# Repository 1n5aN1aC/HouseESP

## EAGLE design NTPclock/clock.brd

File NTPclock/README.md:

TODO:

4 control buttons.
  hour offset
  minute offset
  brightness control
2 segment seperator LEDs
bar graph seconds display.
1 randimizer LED.
12/24h switch

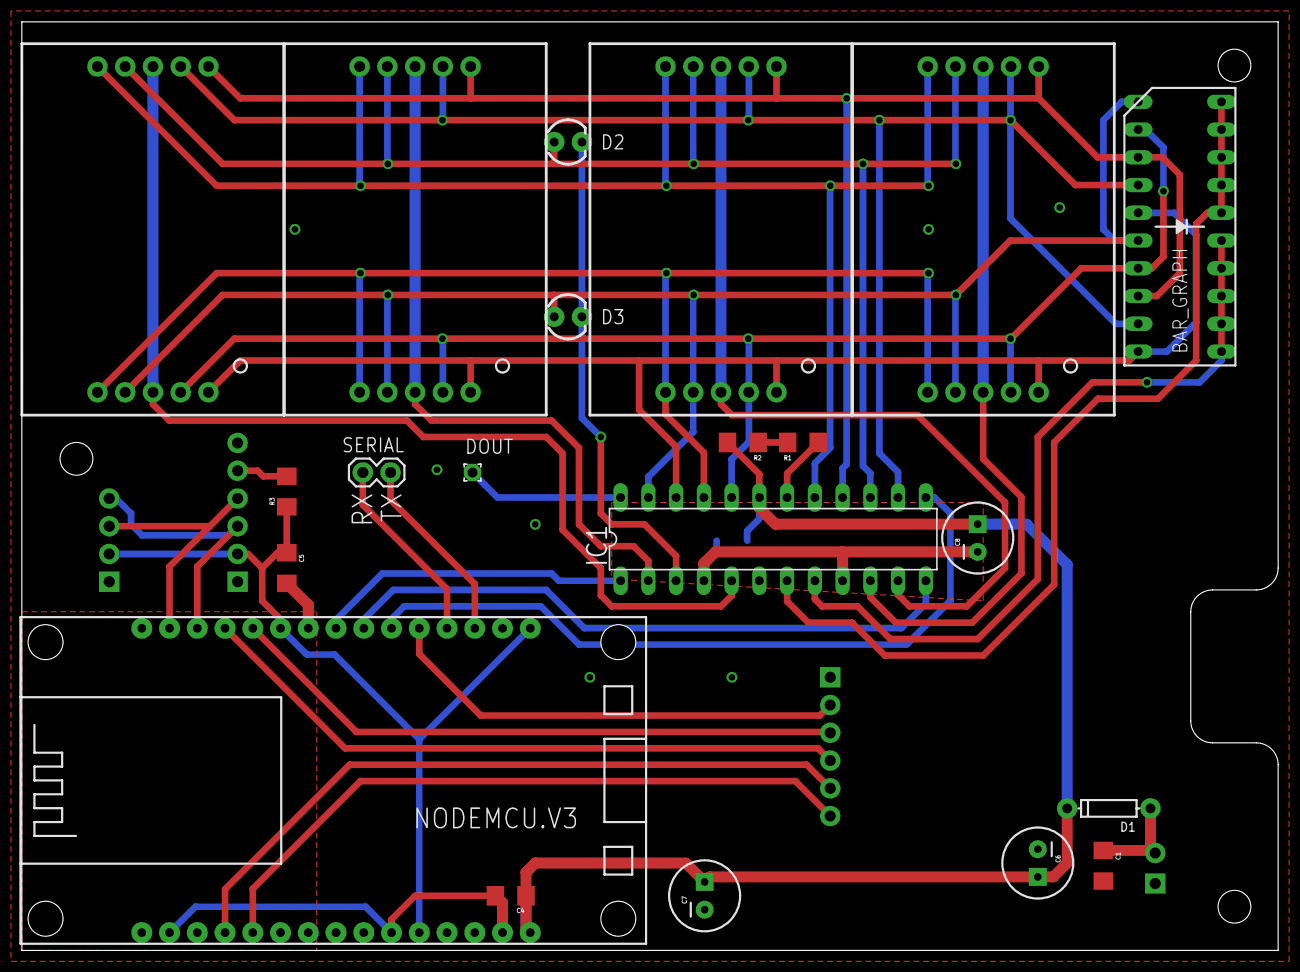
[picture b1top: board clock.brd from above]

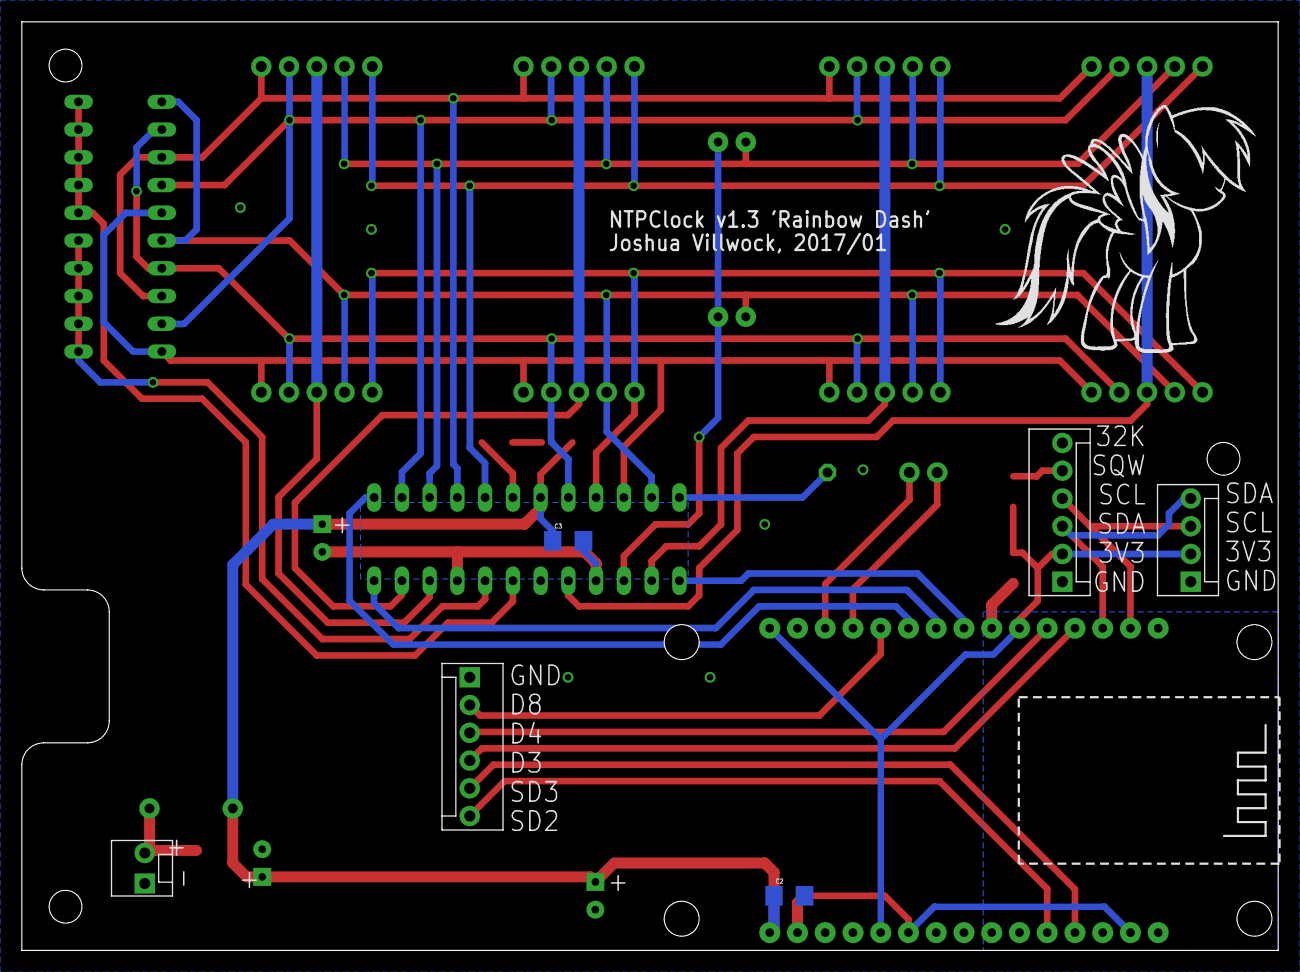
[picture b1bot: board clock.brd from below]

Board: 2 copper layers, 115.0 x 85.0 mm, 28 parts (6 on the bottom side), 35 nets.

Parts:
BAR_GRAPH: LED_BARGAPH_10
BUTTONS: MOLEX-1X6
C1, C4: 10μF; 1206
C2, C3: 0.1μF; 1206
C5: 1mF; 1206
C6: 470μF; CPOL-RADIAL-100UF-25V
C7: 47μF; CPOL-RADIAL-100UF-25V
C8: 10μF; CPOL-RADIAL-100UF-25V
D1: DIODE-1N4148
D2, D3: LED3MM
DIG_0, DIG_1, DIG_2, DIG_3: 7-SEGMENT-DISPLAY-REAL-1"; 7-SEGMENT-REAL-1"
DOUT: 1,6/0,9
FRAME1: FRAME-LETTER; CREATIVE_COMMONS
IC1: MAX7219CNG; DIL24-3
J0: MOLEX-1X6
J1: MOLEX-1X4
NODEMCU.V3: ESP12E_V3_(WIDE); ESP12E_V3_WIDE
POWER: MOLEX-1X2_LOCK
R1, R2: 1206
R3: 10KΩ; 1206
SERIAL: 1X02

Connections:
3.3V: C5.1, J0.2, J1.2, NODEMCU.V3.3V3@0, NODEMCU.V3.3V3@1, NODEMCU.V3.3V3@2, R3.1
A: BAR_GRAPH.4, BAR_GRAPH.9, DIG_0.7, DIG_1.7, DIG_2.7, DIG_3.7, IC1.14
B: BAR_GRAPH.3, BAR_GRAPH.8, DIG_0.6, DIG_1.6, DIG_2.6, DIG_3.6, IC1.16
C: BAR_GRAPH.2, BAR_GRAPH.7, DIG_0.4, DIG_1.4, DIG_2.4, DIG_3.4, IC1.20
CLK: IC1.13, NODEMCU.V3.D7
D: BAR_GRAPH.1, BAR_GRAPH.6, D3.A, DIG_0.2, DIG_1.2, DIG_2.2, DIG_3.2, IC1.23
D3: BUTTONS.4, NODEMCU.V3.D3
D4: BUTTONS.3, NODEMCU.V3.D4
D8: BUTTONS.2, NODEMCU.V3.D8
DATA: IC1.1, NODEMCU.V3.D5
DIGIT0: DIG_1.3, DIG_1.8, IC1.2
DIGIT1: DIG_2.3, DIG_2.8, IC1.11
DIGIT3: BAR_GRAPH.16, BAR_GRAPH.17, BAR_GRAPH.18, BAR_GRAPH.19, BAR_GRAPH.20, IC1.7
DIGIT4: D2.K, D3.K, IC1.3
DIGIT5: DIG_3.3, DIG_3.8, IC1.10
DIGIT6: DIG_0.3, DIG_0.8, IC1.5
DIGIT7: BAR_GRAPH.11, BAR_GRAPH.12, BAR_GRAPH.13, BAR_GRAPH.14, BAR_GRAPH.15, IC1.8
DOUT: DOUT.1, IC1.24
DP: BAR_GRAPH.5, BAR_GRAPH.10, DIG_0.5, DIG_1.5, DIG_2.5, DIG_3.5, IC1.22
E: DIG_0.1, DIG_1.1, DIG_2.1, DIG_3.1, IC1.21
F: D2.A, DIG_0.9, DIG_1.9, DIG_2.9, DIG_3.9, IC1.15
G: DIG_0.10, DIG_1.10, DIG_2.10, DIG_3.10, IC1.17
GND: BUTTONS.1, C1.2, C2.2, C3.2, C4.2, C5.2, C6.2, C7.2, C8.2, IC1.4, IC1.9, J0.1, J1.1, NODEMCU.V3.GND@0, NODEMCU.V3.GND@1, NODEMCU.V3.GND@2, NODEMCU.V3.GND@3, NODEMCU.V3.GND@5, POWER.1
ISET: IC1.18, R1.2
LOAD: IC1.12, NODEMCU.V3.D6
unnamed: R1.1, R2.1
RX: NODEMCU.V3.RX, SERIAL.2
SCL: J0.4, J1.3, NODEMCU.V3.D1
SD2: BUTTONS.6, NODEMCU.V3.SD2
SD3: BUTTONS.5, NODEMCU.V3.SD3
SDA: J0.3, J1.4, NODEMCU.V3.D2
SQW: J0.5, R3.2
TX: NODEMCU.V3.TX, SERIAL.1
VCC: C2.1, C3.1, C4.1, C6.1, C7.1, C8.1, D1.C, IC1.19, NODEMCU.V3.VIN, R2.2
VIN: C1.1, D1.A, POWER.2

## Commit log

2016-11-15 Commit intial code
2016-11-17 Implement cleanup & placeholder code
2016-11-17 Move functionality out to seperate functions
2016-11-18 for loops are good
2016-11-18 Implement bargraph code for seconds.
2016-11-19 Fix Progress bar; switch to hours:minutes
2016-11-19 Initial PCB Design
2016-11-20 Initial board layout
2016-11-20 Change NTP to only update every 6 hours
2016-11-20 Load in RTC time immediently upon start up
    Use that until we get a NTP update.
2016-11-21 Remove stupid String dislay Logic
2016-11-21 Board update
2016-11-21 Switch to alternate RTC library that supports time_t
    (Actually, the other probably would have in a round abut way, but I only
    found out my problem upon switching libraries, and by then it was too
    late.)
2016-11-21 cleaned up code a bit
2016-11-21 Made Wifi optional.
    Should function if no wifi connection
2016-11-22 added comments
2016-11-22 Update Schematic. (Also break it)
2016-11-22 Update Boardfile. (Also break it)
2016-11-22 rearange digits
2016-11-23 Add Ground pour(s)
2016-11-23 Updating pinouts for new PCB layout.
2016-11-24 added buzzer, finished routing ground plane
2016-11-24 added 24 hour toggle support
2016-11-24 Fix military time
2016-11-24 Banished the evil delay() based loops
2016-11-24 Implement : flashing every second
2016-11-25 Correct borders
2016-11-25 minor cosmetic changes
2016-11-25 Correct size of LEDs. Also reroute entire LED area.
2016-11-26 Made brightness more modular
2016-11-26 removed #define to save space
    Not needed for new RTC library
2016-11-26 Re-organize Schematic. Add license.
2016-11-27 organize schematic more
2016-12-03 Silkscreen Labeling improvements
2016-12-03 Physical Layer improvements.
2016-12-03 Added Serial Breakout
2016-12-03 Fix serial labeling
2016-12-03 minor silkscreen improvements
2016-12-04 Correct bar graph ordering
2016-12-05 enable ground pour around lcds
2016-12-05 Remove Buzzer, add button panel
2016-12-05 Reorganize panel,
2016-12-06 Silkscreen changes
2016-12-06 add text to button connector
2016-12-06 Added input protection
2016-12-06 Small power delivery improvements
2016-12-09 temp
2016-12-10 Break all modules out into their own files.
2016-12-10 Update Licensing information
2016-12-10 Cleanup before troubleshooting
2016-12-10 Fixed stupid DS3232 bug
2016-12-12 Implement non-blocking MQTT reconnection
2016-12-12 add publish function
2016-12-13 fix MQTT
2016-12-13 Add RTC temp sent via MQTT every 10 seconds
2016-12-14 seperated loop into functions
2016-12-14 broke stuff
2016-12-16 poop
2016-12-16 Aparently, the server IP has to be a special type
2016-12-16 quick fix?
2016-12-16 define cleanup
2016-12-16 Fixed subscribing
2016-12-16 working mqtt subscriptions
2016-12-18 Fixed callbacks; spelling fixes.
2016-12-18 Added working bi-directional brightness control
2016-12-18 added retained mesage functionality
2016-12-18 Add new set_brightness function that also updates MQTT
2016-12-19 Added preliminary code for the attic controller
2016-12-21 Added roof_sensor_serial
    I'm much more proud of this code, than any of my ESP code......
2016-12-21 Updated Attic Controller to not chew power
2016-12-21 Roof_sensor now sends one measurement per line
2016-12-22 add serial reading functionality
2016-12-22 Standardize serial printing modes
2016-12-22 Abstracted battery volatge for roof
2016-12-22 Added MQTT publishing of roof serial data
2016-12-23 Added Power Monitor sketch outline
2016-12-23 Attic Controller Updates?
2016-12-24 Adjust telemetry timings for roof sensor
2016-12-26 fix battery checker bug.
2016-12-27 Added capacitor values
2016-12-27 Unit fixes
2016-12-27 added more gitignore lines
2016-12-27 Filter out erroneous static-related rain triggers
2016-12-27 Add v1.0 logo to board
2016-12-31 add comment & debug
2016-12-31 Clean up options in attic controller
2016-12-31 Add options file for NTPclock
2016-12-31 only save time 1x day & Cleanup
2016-12-31 correct rain sensor output
2016-12-31 reconnect MQTT faster on attic controller
2017-01-03 Add slight delays to all main loops.
    This saves considerable power & heat- Makes readings more accurate
2017-01-03 Set ESP devices to custom hostnames
2017-01-03 Added .zip for Finished PCB Gerbers
2017-01-07 Power Monitor updates
2017-01-20 Begin updating the Board file for the cheaper V3
2017-01-20 Updated NTPclock for new fotprint
2017-01-20 Updated NTPclock for new footprint
2017-03-16 Removed unneeded debug
2017-11-11 Wemos D1 mini has a different pinout.
2017-11-11 add comments for future
2017-11-12 Fix extra space padding & simplify temp conversion
2018-03-11 Disable Silly AP on attic controller
2018-03-11 Create Micro_Temp project
2018-03-11 Enable deep sleep
2018-03-11 Fixed MQTT posting
2018-03-11 Set to 5 minutes
2018-03-12 add batt readings
2018-03-12 Revert "add batt readings"
    This reverts commit 22afdbb811d28f8e1709133fda770044d0fd18db.
2018-03-12 Revert "Revert "add batt readings""
    This reverts commit 9fc677f1f726b4ce519adb5703dff3d9fc42397c.
2018-03-12 Revert "Revert "Revert "add batt readings"""
    This reverts commit c52cc3b7ff764c1c1837b84c5e691d25f891088b.
2019-03-17 move MQTT options to options file
2019-03-17 Revert "move MQTT options to options file"
    This reverts commit 708b7fd3ac6fbb87d8506dfeb49a734e627fc980.
2019-03-17 Correct ordering for strict compilers
2019-03-17 add header file for main c file
2019-03-17 readability change
2019-05-29 imital computer switch
2019-05-30 First full test
2019-05-30 remove stuff
2019-05-31 move away from aRest library.
2019-06-01 add arp sending task
2019-06-13 Remove old timer library
2019-06-13 Implement temperature reading
2019-06-13 Implement sending temps to server
2019-06-13 Fix SendGratuitousARP()
2019-07-20 Update to final influxDB databases
2019-07-20 Remove MQTT for InfluxDB
2020-09-11 Switch reorganization
    to prepare for OTA
2020-09-11 Move to generic Options File
2020-09-11 Complete Adding OTA
2020-09-14 Add LORA_Water_Sensor
2020-09-14 Update to make it work
2020-09-21 deep sleep testingg
2020-09-21 Add OTA to AtticController

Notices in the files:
parts and their libraries:
SparkFun-Resistors: Licensing: Creative Commons ShareAlike 4.0 International - https://creativecommons.org/licenses/by-sa/4.0
SparkFun-Aesthetics: Released under the Creative Commons Attribution Share-Alike 4.0 License
SparkFun-Aesthetics: https://creativecommons.org/licenses/by-sa/4.0
